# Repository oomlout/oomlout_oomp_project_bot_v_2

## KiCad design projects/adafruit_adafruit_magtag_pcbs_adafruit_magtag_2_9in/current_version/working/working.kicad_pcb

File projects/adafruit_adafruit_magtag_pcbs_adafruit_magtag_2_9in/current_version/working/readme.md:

# adafruit_magtag_pcbs
 
## summary 
* id: adafruit_adafruit_magtag_pcbs_adafruit_magtag_2_9in
* user: adafruit
* name: adafruit_magtag_pcbs
* board: adafruit_magtag_2_9in
* repo: https://github.com/adafruit/Adafruit_MagTag_PCBs

* src_file_repo_sch: 
* src_file_repo_sch_link: https://github.com/adafruit/Adafruit_MagTag_PCBs/tree/main/
* full details link: https://github.com/oomlout/oomlout_oomp_project_bot_v_2/tree/main/projects/adafruit_adafruit_magtag_pcbs_adafruit_magtag_2_9in/current_version/working  

## schematic  
  
[schematic (pdf)](working_schematic.pdf) 

## pcb  

[board (pdf)](working.pdf)  

## working_bom
| Id | Designator | Footprint | Quantity | Designation | Supplier and ref |  | None | 
| --- | --- | --- | --- | --- | --- | --- | --- | 
| 1 | D2,D5,D3 | SOD-123 | 3 | MBR0530 |  |  | [''] | 
| 2 | R7,R20,R5,R2,R9,R1 | 0603-NO | 6 | 10K |  |  | [''] | 
| 3 | C25,C24,C19,C23,C26,C31,C28,C30,C27 | 0805-NO | 9 | 1uF |  |  | [''] | 
| 4 | R18,R16 | 0603-NO | 2 | 1K |  |  | [''] | 
| 5 | C9 | 0805-NO | 1 | 10uF/10V+ |  |  | [''] | 
| 6 | Q3,Q1 | SOT23-R | 2 | DMG3415U-7 |  |  | [''] | 
| 7 | C6,C14,C12 | 0603-NO | 3 | 1uF |  |  | [''] | 
| 8 | R24,R22,R25,R23 | 0603-NO | 4 | DNP |  |  | [''] | 
| 9 | SJ2 | SOLDERJUMPER_2WAY_OPEN_NOPASTE | 1 |  |  |  | [''] | 
| 10 | ON0 | CHIPLED_0603_NOOUTLINE | 1 | GREEN |  |  | [''] | 
| 11 | U4 | SOT23-5 | 1 | AP2112K-3.3 |  |  | [''] | 
| 12 | TP6,TP1,TP7,TP8 | TESTPOINT_ROUND_1.5MM_NO | 4 |  |  |  | [''] | 
| 13 | C8,C7,C11,C13,C17,C10,C18,C3,C4 | 0805-NO | 9 | 10ÂµF |  |  | [''] | 
| 14 | R11,R17,R10 | 0603-NO | 3 | 1Meg |  |  | [''] | 
| 15 | L1 | INDUCTOR_4X4MM_NR401 | 1 | 10uH |  |  | [''] | 
| 16 | D1,D6 | SOD-323 | 2 | 3.6V |  |  | [''] | 
| 17 | U$15 | PCBFEAT-REV-040 | 1 |  |  |  | [''] | 
| 18 | IC2 | SOT23-6 | 1 | PAM8301 |  |  | [''] | 
| 19 | L0 | CHIPLED_0603_NOOUTLINE | 1 | RED |  |  | [''] | 
| 20 | R14,R12 | 0603-NO | 2 | 100k |  |  | [''] | 
| 21 | IC4 | LGA16_3X3MM | 1 | LIS3DH |  |  | [''] | 
| 22 | C1,C20 | 0805-NO | 2 | 10uF |  |  | [''] | 
| 23 | TP2,TP4,TP5,TP3 | SMT_NUT_3MM | 4 | SEWTAP_SMTNUTM3 |  |  | [''] | 
| 24 | R21 | 0805_10MGAP | 1 | DNP |  |  | [''] | 
| 25 | R27,R15,R26 | 0603-NO | 3 | 100K |  |  | [''] | 
| 26 | Q2 | SOT23-R | 1 | DMG3415 |  |  | [''] | 
| 27 | C21,C5,C15,C16,C2 | 0603-NO | 5 | 0.1uF |  |  | [''] | 
| 28 | R19,R6 | 0603-NO | 2 | 47K |  |  | [''] | 
| 29 | U3 | MODULE_ESP32-S2-WROVER | 1 | ESP32-S2-WROVER |  |  | [''] | 
| 30 | CONN1 | JST_SH4 | 1 | STEMMA_I2C_QT |  |  | [''] | 
| 31 | SW3,SW1 | SPST_TACTILE_RA | 2 | RA_TACT |  |  | [''] | 
| 32 | R13 | 0805_10MGAP | 1 | 0.47ohm |  |  | [''] | 
| 33 | U2 | SOT23-5 | 1 | MCP73831T-2ACI/OT |  |  | [''] | 
| 34 | FID3,FID1,FID2,FID4,FID6,FID5 | FIDUCIAL_1MM | 6 | FIDUCIAL_1MM |  |  | [''] | 
| 35 | JP2 | 1X02_ROUND | 1 | UART |  |  | [''] | 
| 36 | C29 | 0805-NO | 1 | 4.7uF/25V |  |  | [''] | 
| 37 | X4 | USB_C_CUSB31-CFM2AX-01-X | 1 | USB C |  |  | [''] | 
| 38 | SW4 | SPDT_SMT_SSSS811101 | 1 | SPDT R/A |  |  | [''] | 
| 39 | SP1 | BUZZER_SMT_7.5MM | 1 | 7.5mm SPK |  |  | [''] | 
| 40 | X1 | JSTPH2_BATT | 1 | JSTPH |  |  | [''] | 
| 41 | D4 | SOD-123 | 1 | MBR540 |  |  | [''] | 
| 42 | SENSE0,SENSE1 | JSTPH3 | 2 | JST PH 3 |  |  | [''] | 
| 43 | R4 | 0603-NO | 1 | 5.1k |  |  | [''] | 
| 44 | U$70 | MAGTAG_FRONT | 1 |  |  |  | [''] | 
| 45 | R8,R3 | 0603-NO | 2 | 5.1K |  |  | [''] | 
| 46 | Q5 | SOT23-3 | 1 | IRLML0100 |  |  | [''] | 
| 47 | CHG1 | CHIPLED_0603_NOOUTLINE | 1 | ORANGE |  |  | [''] | 
| 48 | LED4,LED3,LED2,LED5 | WS2812B_4020 | 4 | WS2812B_4020 |  |  | [''] | 
| 49 | SW2,SW5,SW6,SW7 | TACTILE_3X6MM | 4 |  |  |  | [''] | 
| 50 | U$69 | MAGTAG_BOTTOM | 1 |  |  |  | [''] | 
| 51 | U1 | ALS-PT19-315C | 1 |  |  |  | [''] | 
| 52 | EINK2 | EINK_290IN | 1 | EINK_24PIN_290IN |  |  | [''] | 

## bom_schematic
| Ref | Qnty | Value | Cmp name | Footprint | Description | Vendor | DNP | 
| --- | --- | --- | --- | --- | --- | --- | --- | 
| C1, C20 | 2 | 10uF | CAP_CERAMIC0805-NOOUTLINE | working:0805-NO |  |  |  | 
| C2, C5, C15, C16, C21 | 5 | 0.1uF | CAP_CERAMIC0603_NO | working:0603-NO |  |  |  | 
| C3, C4, C7, C8, C10, C11, C13, C17, C18 | 9 | 10ÂµF | CAP_CERAMIC0805-NOOUTLINE | working:0805-NO |  |  |  | 
| C6, C12, C14 | 3 | 1uF | CAP_CERAMIC0603_NO | working:0603-NO |  |  |  | 
| C9 | 1 | 10uF/10V+ | CAP_CERAMIC0805-NOOUTLINE | working:0805-NO |  |  |  | 
| C19, C23, C24, C25, C26, C27, C28, C30, C31 | 9 | 1uF | CAP_CERAMIC0805-NOOUTLINE | working:0805-NO |  |  |  | 
| C29 | 1 | 4.7uF/25V | CAP_CERAMIC0805-NOOUTLINE | working:0805-NO |  |  |  | 
| CHG1 | 1 | ORANGE | LED0603_NOOUTLINE | working:CHIPLED_0603_NOOUTLINE |  |  |  | 
| CONN1 | 1 | STEMMA_I2C_QT | STEMMA_I2C_QT | working:JST_SH4 |  |  |  | 
| D1, D6 | 2 | 3.6V | DIODE-ZENERSOD323 | working:SOD-323 |  |  |  | 
| D2, D3, D5 | 3 | MBR0530 | DIODE-SCHOTTKYSOD-123 | working:SOD-123 |  |  |  | 
| D4 | 1 | MBR540 | DIODE-SCHOTTKYSOD-123 | working:SOD-123 |  |  |  | 
| EINK2 | 1 | EINK_24PIN_290IN | EINK_24PIN_290IN | working:EINK_290IN |  |  |  | 
| FID1, FID2, FID3, FID4, FID5, FID6 | 6 | FIDUCIAL_1MM | FIDUCIAL_1MM | working:FIDUCIAL_1MM |  |  |  | 
| IC2 | 1 | PAM8301 | PAM8301 | working:SOT23-6 |  |  |  | 
| IC4 | 1 | LIS3DH | ACCEL_LIS3DHTR | working:LGA16_3X3MM |  |  |  | 
| JP2 | 1 | UART | HEADER-1X2ROUND | working:1X02_ROUND |  |  |  | 
| L0 | 1 | RED | LED0603_NOOUTLINE | working:CHIPLED_0603_NOOUTLINE |  |  |  | 
| L1 | 1 | 10uH | INDUCTORNR401 | working:INDUCTOR_4X4MM_NR401 |  |  |  | 
| LED2, LED3, LED4, LED5 | 4 | WS2812B_4020 | WS2812B_4020 | working:WS2812B_4020 |  |  |  | 
| ON0 | 1 | GREEN | LED0603_NOOUTLINE | working:CHIPLED_0603_NOOUTLINE |  |  |  | 
| Q1, Q3 | 2 | DMG3415U-7 | MOSFET-P | working:SOT23-R |  |  |  | 
| Q2 | 1 | DMG3415 | MOSFET-P | working:SOT23-R |  |  |  | 
| Q5 | 1 | IRLML2060TRPBF | IRLML2060TRPBF | working:SOT23-3 |  |  |  | 
| R1, R2, R5, R7, R9, R20 | 6 | 10K | RESISTOR_0603_NOOUT | working:0603-NO |  |  |  | 
| R3, R8 | 2 | 5.1K | RESISTOR_0603_NOOUT | working:0603-NO |  |  |  | 
| R4 | 1 | 5.1k | RESISTOR_0603_NOOUT | working:0603-NO |  |  |  | 
| R6, R19 | 2 | 47K | RESISTOR_0603_NOOUT | working:0603-NO |  |  |  | 
| R10, R11, R17 | 3 | 1Meg | RESISTOR_0603_NOOUT | working:0603-NO |  |  |  | 
| R12, R14 | 2 | 100k | RESISTOR_0603_NOOUT | working:0603-NO |  |  |  | 
| R13 | 1 | 0.47ohm | RESISTOR0805_10MGAP | working:0805_10MGAP |  |  |  | 
| R15, R26, R27 | 3 | 100K | RESISTOR_0603_NOOUT | working:0603-NO |  |  |  | 
| R16, R18 | 2 | 1K | RESISTOR_0603_NOOUT | working:0603-NO |  |  |  | 
| R21 | 1 | DNP | RESISTOR0805_10MGAP | working:0805_10MGAP |  |  |  | 
| R22, R23, R24, R25 | 4 | DNP | RESISTOR_0603_NOOUT | working:0603-NO |  |  |  | 
| SENSE0, SENSE1 | 2 | JST PH 3 | CON_JST_PH_3PIN | working:JSTPH3 |  |  |  | 
| SJ2 | 1 | SOLDERJUMPER_2WAY | SOLDERJUMPER_2WAY | working:SOLDERJUMPER_2WAY_OPEN_NOPASTE |  |  |  | 
| SP1 | 1 | SPEAKER_7.5MM | SPEAKER_7.5MM | working:BUZZER_SMT_7.5MM |  |  |  | 
| SW1, SW3 | 2 | RA_TACT | SWITCH_SPST_TACT_RA | working:SPST_TACTILE_RA |  |  |  | 
| SW2, SW5, SW6, SW7 | 4 | SWITCH_PUSHBUTTON_3.5X6MM | SWITCH_PUSHBUTTON_3.5X6MM | working:TACTILE_3X6MM |  |  |  | 
| SW4 | 1 | SPDT R/A | SWITCH_SPDT | working:SPDT_SMT_SSSS811101 |  |  |  | 
| TP1, TP6, TP7, TP8 | 4 | TESTPOINTROUND1.5MMNO | TESTPOINTROUND1.5MMNO | working:TESTPOINT_ROUND_1.5MM_NO |  |  |  | 
| TP2, TP3, TP4, TP5 | 4 | SEWTAP_SMTNUTM3 | SEWTAP_SMTNUTM3 | working:SMT_NUT_3MM |  |  |  | 
| U1 | 1 | PHOTOTRANSISTOR_PT19-315C | PHOTOTRANSISTOR_PT19-315C | working:ALS-PT19-315C |  |  |  | 
| U2 | 1 | MCP73831T-2ACI/OT | MCP73831/2 | working:SOT23-5 |  |  |  | 
| U3 | 1 | ESP32-S2-WROVER | ESP32-S2-WROVER | working:MODULE_ESP32-S2-WROVER |  |  |  | 
| U4 | 1 | AP2112K-3.3 | VREG_SOT23-5 | working:SOT23-5 |  |  |  | 
| X1 | 1 | JSTPH | CON_JST_PH_2PIN_BATT | working:JSTPH2_BATT |  |  |  | 
| X4 | 1 | USB C | USB_C | working:USB_C_CUSB31-CFM2AX-01-X |  |  |  |

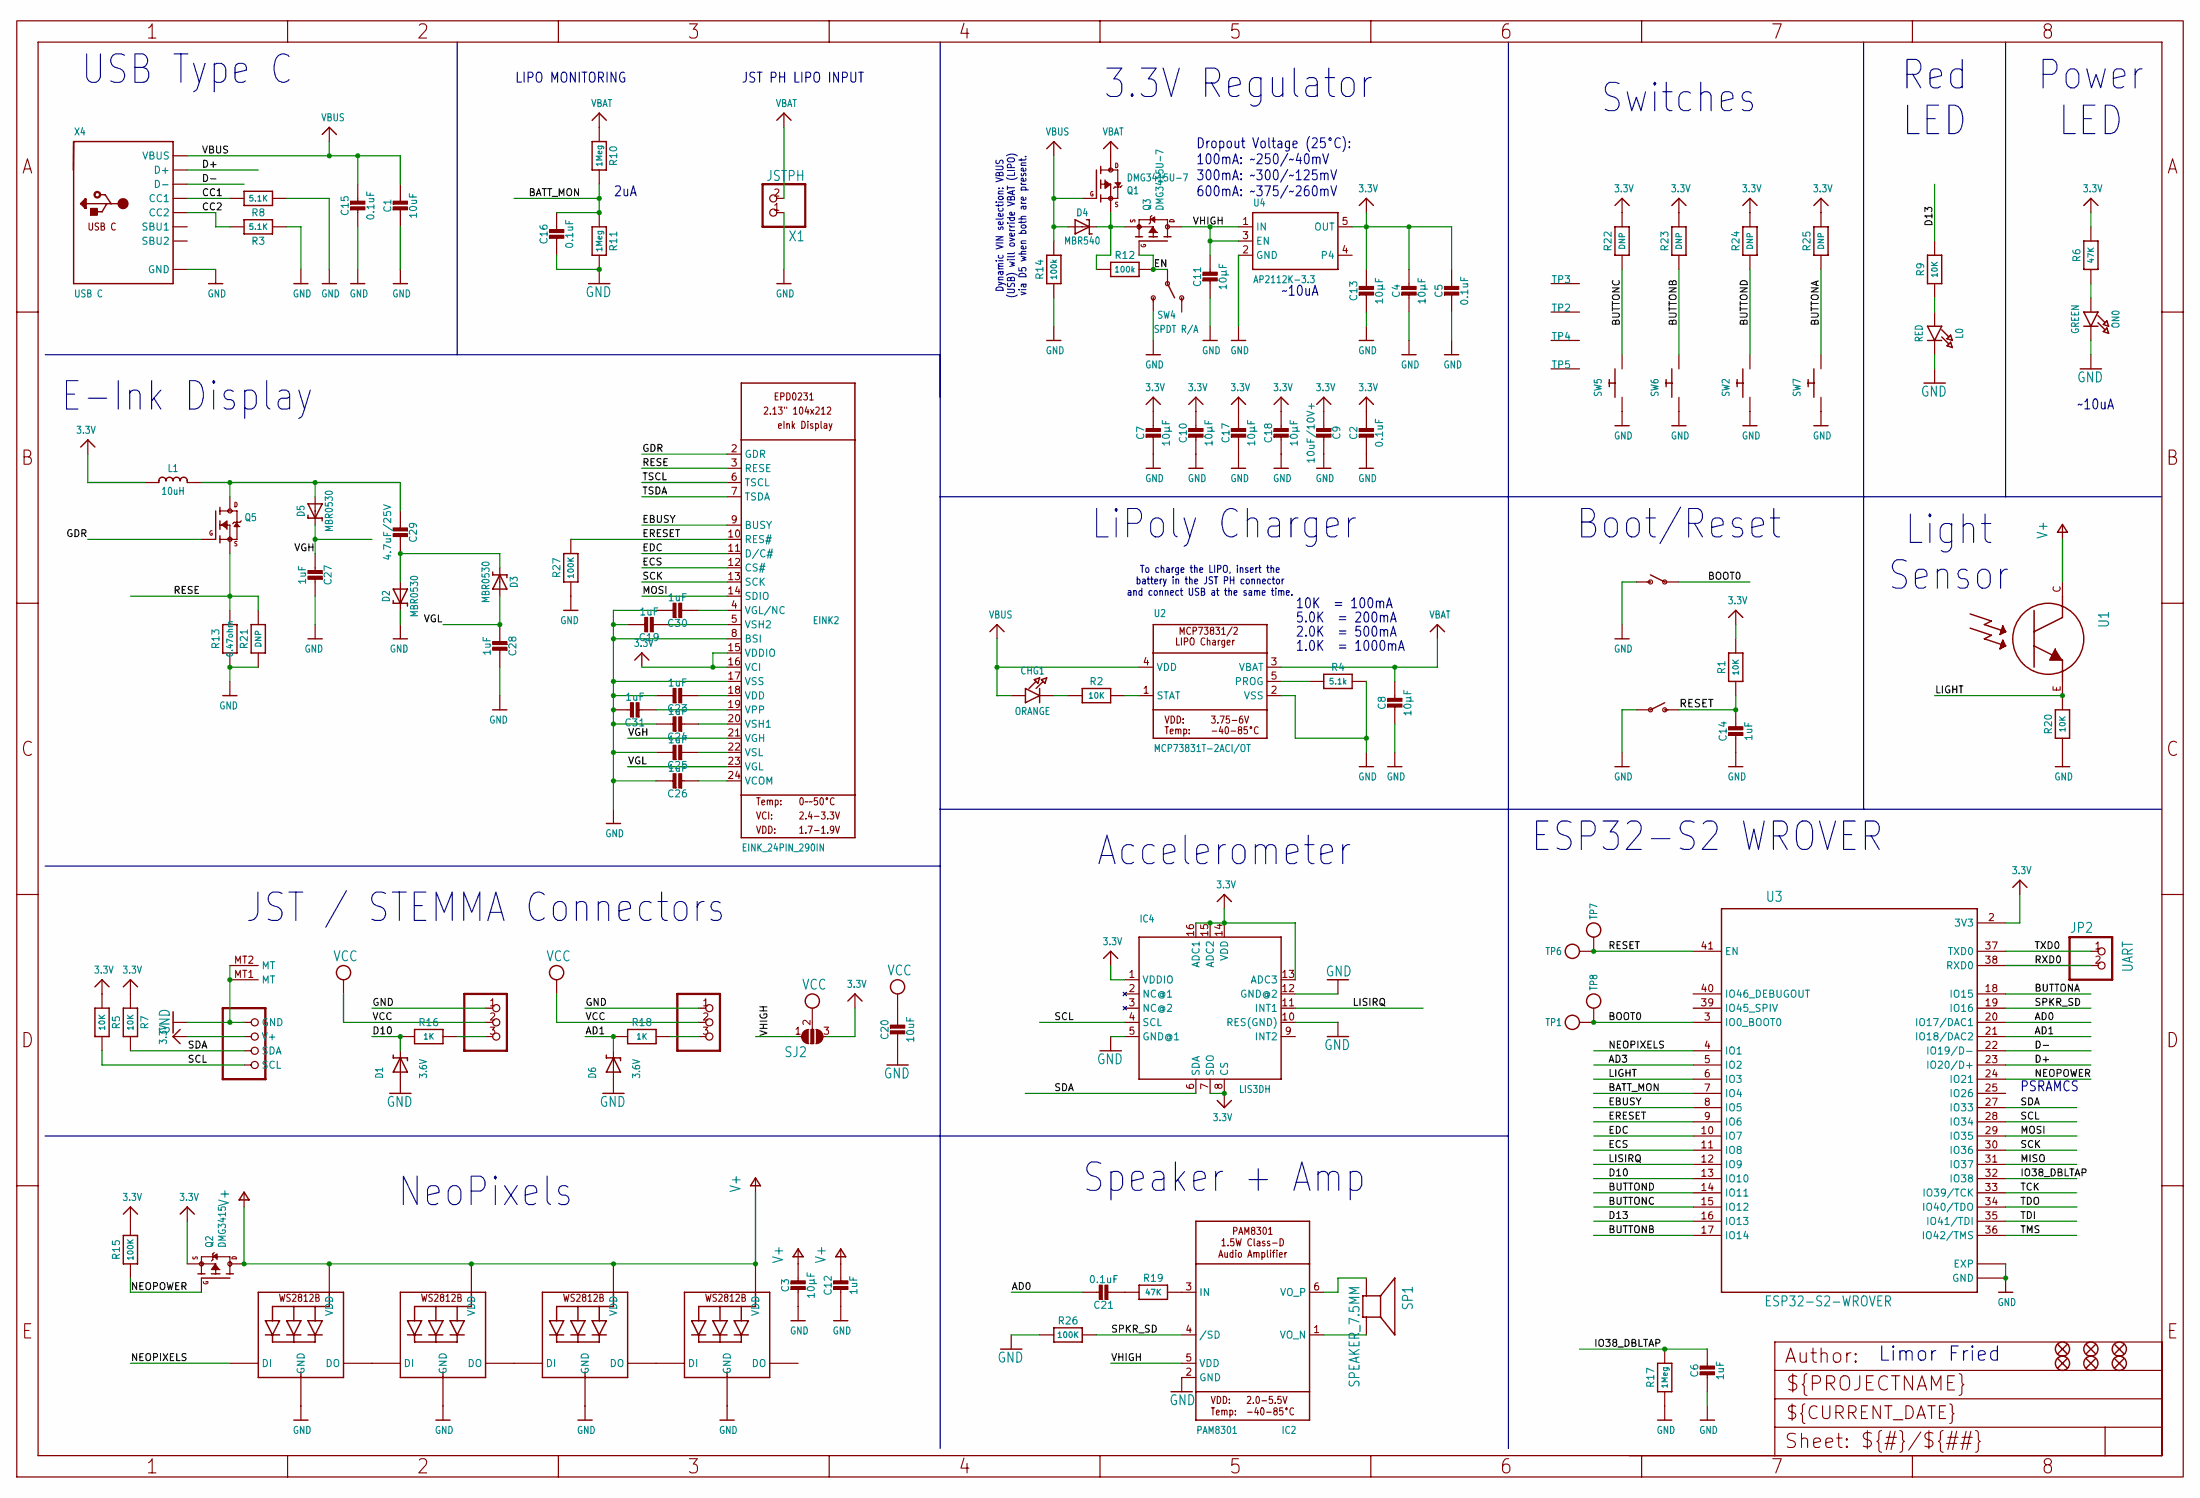
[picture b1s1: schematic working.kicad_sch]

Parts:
C1, C20: 10uF; 0805-NO
C2, C5, C15, C16, C21: 0.1uF; 0603-NO
C3, C4, C7, C8, C10, C11, C13, C17, C18: 10µF; 0805-NO
C6, C12, C14: 1uF; 0603-NO
C9: 10uF/10V+; 0805-NO
C19, C23, C24, C25, C26, C27, C28, C30, C31: 1uF; 0805-NO
C29: 4.7uF/25V; 0805-NO
CHG1: ORANGE; CHIPLED_0603_NOOUTLINE
CONN1: STEMMA_I2C_QT; JST_SH4
D1, D6: 3.6V; SOD-323
D2, D3, D5: MBR0530; SOD-123
D4: MBR540; SOD-123
EINK2: EINK_24PIN_290IN; EINK_290IN
FID1, FID2, FID3, FID4, FID5, FID6: FIDUCIAL_1MM
IC2: PAM8301; SOT23-6
IC4: LIS3DH; LGA16_3X3MM
JP2: UART; 1X02_ROUND
L0: RED; CHIPLED_0603_NOOUTLINE
L1: 10uH; INDUCTOR_4X4MM_NR401
LED2, LED3, LED4, LED5: WS2812B_4020
ON0: GREEN; CHIPLED_0603_NOOUTLINE
Q1, Q3: DMG3415U-7; SOT23-R
Q2: DMG3415; SOT23-R
Q5: IRLML2060TRPBF; SOT23-3
R1, R2, R5, R7, R9, R20: 10K; 0603-NO
R3, R8: 5.1K; 0603-NO
R4: 5.1k; 0603-NO
R6, R19: 47K; 0603-NO
R10, R11, R17: 1Meg; 0603-NO
R12, R14: 100k; 0603-NO
R13: 0.47ohm; 0805_10MGAP
R15, R26, R27: 100K; 0603-NO
R16, R18: 1K; 0603-NO
R21: DNP; 0805_10MGAP
R22, R23, R24, R25: DNP; 0603-NO
SENSE0, SENSE1: JST PH 3; JSTPH3
SJ2: SOLDERJUMPER_2WAY; SOLDERJUMPER_2WAY_OPEN_NOPASTE
SP1: SPEAKER_7.5MM; BUZZER_SMT_7.5MM
SW1, SW3: RA_TACT; SPST_TACTILE_RA
SW2, SW5, SW6, SW7: SWITCH_PUSHBUTTON_3.5X6MM; TACTILE_3X6MM
SW4: SPDT R/A; SPDT_SMT_SSSS811101
TP1, TP6, TP7, TP8: TESTPOINTROUND1.5MMNO; TESTPOINT_ROUND_1.5MM_NO
TP2, TP3, TP4, TP5: SEWTAP_SMTNUTM3; SMT_NUT_3MM
U1: PHOTOTRANSISTOR_PT19-315C; ALS-PT19-315C
U2: MCP73831T-2ACI/OT; SOT23-5
U3: ESP32-S2-WROVER; MODULE_ESP32-S2-WROVER
U4: AP2112K-3.3; SOT23-5
X1: JSTPH; JSTPH2_BATT
X4: USB C; USB_C_CUSB31-CFM2AX-01-X

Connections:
3.3V: C2.1, C4.1, C5.1, C7.1, C9.2, C10.1, C13.1, C17.1, C18.1, CONN1.2 (V+), EINK2.15 (VDDIO), EINK2.16 (VCI), IC4.1 (VDDIO), IC4.7 (SDO), IC4.8 (CS), IC4.13 (ADC3), IC4.14 (VDD), IC4.15 (ADC2), IC4.16 (ADC1), L1.P$2 (2), Q2.2 (S), R1.2, R5.1, R6.2, R7.1, R15.2, R22.2, R23.2, R24.2, R25.2, SJ2.3, U3.2 (3V3), U4.5 (OUT)
A1_JST1: R18.1, SENSE1.3
AD0: C21.1, U3.20 (IO17/DAC1)
AD1: D6.C, R18.2, U3.21 (IO18/DAC2)
AD3: U3.5 (IO2)
BATT_MON: C16.1, R10.2, R11.1, U3.7 (IO4)
BOOT0: SW1.1, TP1.P$1, TP8.P$1, U3.3 (IO0_BOOT0)
BUTTONA: R25.1, SW7.P$2, U3.18 (IO15)
BUTTONB: R23.1, SW6.P$2, U3.17 (IO14)
BUTTONC: R22.1, SW5.P$2, U3.15 (IO12)
BUTTOND: R24.1, SW2.P$2, U3.14 (IO11)
CC1: R8.2, X4.A5 (CC1)
CC2: R3.2, X4.B5 (CC2)
D10: D1.C, R16.2, U3.13 (IO10)
D10_JST: R16.1, SENSE0.3
D13: R9.2, U3.16 (IO13)
D+: U3.23 (IO20/D+), X4.A6 (D+), X4.B6 (D+)
D-: U3.22 (IO19/D-), X4.A7 (D-), X4.B7 (D-)
EBUSY: EINK2.9 (BUSY), U3.8 (IO5)
ECS: EINK2.12 (CS#), U3.11 (IO8)
EDC: EINK2.11 (D/C#), U3.10 (IO7)
EN: Q3.1 (G), R12.2, SW4.B
ERESET: EINK2.10 (RES#), R27.2, U3.9 (IO6)
GDR: EINK2.2 (GDR), Q5.1 (G)
GND: C1.2, C2.2, C3.2, C4.2, C5.2, C6.2, C7.2, C8.2, C9.1, C10.2, C11.2, C12.2, C13.2, C14.2, C15.2, C16.2, C17.2, C18.2, C19.1, C20.2, C23.1, C24.1, C25.1, C26.1, C27.2, C28.2, C30.1, C31.1, CONN1.1 (GND), CONN1.MT1 (MT), CONN1.MT2 (MT), D1.A, D2.C, D6.A, EINK2.8 (BSI), EINK2.17 (VSS), IC2.2 (GND), IC4.5 (GND@1), IC4.10 (RES(GND)), IC4.12 (GND@2), L0.C, LED2.4 (GND), LED3.4 (GND), LED4.4 (GND), LED5.4 (GND), ON0.C, R3.1, R4.2, R8.1, R11.2, R13.2, R14.1, R17.1, R20.1, R21.2, R26.1, R27.1, SENSE0.1, SENSE1.1, SW1.2 (S), SW2.P$1, SW3.1, SW4.C (S), SW5.P$1, SW6.P$1, SW7.P$1, U2.2 (VSS), U3.1 (GND), U3.26 (GND), U3.42 (GND), U3.43_1 (EXP), U3.43_2 (EXP), U3.43_3 (EXP), U3.43_4 (EXP), U3.43_5 (EXP), U3.43_6 (EXP), U3.43_7 (EXP), U3.43_8 (EXP), U3.43_9 (EXP), U3.43_10 (EXP)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
IO38_DBLTAP: C6.1, R17.2, U3.32 (IO38)
LIGHT: R20.2, U1.E, U3.6 (IO3)
LISIRQ: IC4.11 (INT1), U3.12 (IO9)
MISO: U3.31 (IO37)
MOSI: EINK2.14 (SDIO), U3.29 (IO35)
unnamed: L0.A, R9.1
unnamed: LED2.3 (DO), LED3.1 (DI)
unnamed: ON0.A, R6.1
unnamed: CHG1.C, R2.1
unnamed: C21.2, R19.1
unnamed: R2.2, U2.1 (STAT)
unnamed: IC2.3 (IN), R19.2
unnamed: R4.1, U2.5 (PROG)
unnamed: C19.2, EINK2.5 (VSH2)
unnamed: C23.2, EINK2.18 (VDD)
unnamed: C24.2, EINK2.20 (VSH1)
unnamed: LED4.3 (DO), LED5.1 (DI)
unnamed: C29.2, D2.A, D3.C
unnamed: C29.1, D5.A, L1.P$1 (1), Q5.3 (D)
unnamed: C30.2, EINK2.4 (VGL/NC)
unnamed: C31.2, EINK2.19 (VPP)
unnamed: LED3.3 (DO), LED4.1 (DI)
unnamed: IC2.1 (VO_N), SP1.-
unnamed: IC2.6 (VO_P), SP1.+
unnamed: D4.C, Q1.2 (S), Q3.2 (S), R12.1
unnamed: C25.2, EINK2.22 (VSL)
unnamed: C26.2, EINK2.24 (VCOM)
NEOPIXELS: LED2.1 (DI), U3.4 (IO1)
NEOPOWER: Q2.1 (G), R15.1, U3.24 (IO21)
RESE: EINK2.3 (RESE), Q5.2 (S), R13.1, R21.1
RESET: C14.1, R1.1, SW3.2 (S), TP6.P$1, TP7.P$1, U3.41 (EN)
RXD0: JP2.2, U3.38 (RXD0)
SCK: EINK2.13 (SCK), U3.30 (IO36)
SCL: CONN1.4 (SCL), IC4.4 (SCL), R5.2, U3.28 (IO34)
SDA: CONN1.3 (SDA), IC4.6 (SDA), R7.2, U3.27 (IO33)
SPKR_SD: IC2.4 (/SD), R26.2, U3.19 (IO16)
TCK: U3.33 (IO39/TCK)
TDI: U3.35 (IO41/TDI)
TDO: U3.34 (IO40/TDO)
TMS: U3.36 (IO42/TMS)
TSCL: EINK2.6 (TSCL)
TSDA: EINK2.7 (TSDA)
TXD0: JP2.1, U3.37 (TXD0)
V+: C3.1, C12.1, LED2.2 (VDD), LED3.2 (VDD), LED4.2 (VDD), LED5.2 (VDD), Q2.3 (D), U1.C
VBAT: C8.1, Q1.3 (D), R10.1, U2.3 (VBAT), X1.2
VBUS: C1.1, C15.1, CHG1.A, D4.A, Q1.1 (G), R14.2, U2.4 (VDD), X4.A4B9 (VBUS), X4.B4A9 (VBUS)
VCC: C20.1, SENSE0.2, SENSE1.2, SJ2.2
VGH: C27.1, D5.C, EINK2.21 (VGH)
VGL: C28.1, D3.A, EINK2.23 (VGL)
VHIGH: C11.1, IC2.5 (VDD), Q3.3 (D), SJ2.1, U4.1 (IN), U4.3 (EN)

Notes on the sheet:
USB Type C
Dropout Voltage (25°C): 100mA: ~250/~40mV 300mA: ~300/~125mV 600mA: ~375/~260mV
Power LED
Accelerometer
1.0K = 1000mA
JST / STEMMA Connectors
Red LED
Dynamic VIN selection: VBUS (USB) will override VBAT (LIPO) via D5 when both are present.
Limor Fried
Light Sensor
~10uA
LiPoly Charger
Boot/Reset
2uA
5.0K = 200mA
ESP32-S2 WROVER
Switches
3.3V Regulator
Speaker + Amp
LIPO MONITORING
E-Ink Display
To charge the LIPO, insert the battery in the JST PH connector and connect USB at the same time.
NeoPixels
JST PH LIPO INPUT
10K = 100mA
2.0K = 500mA
PSRAMCS

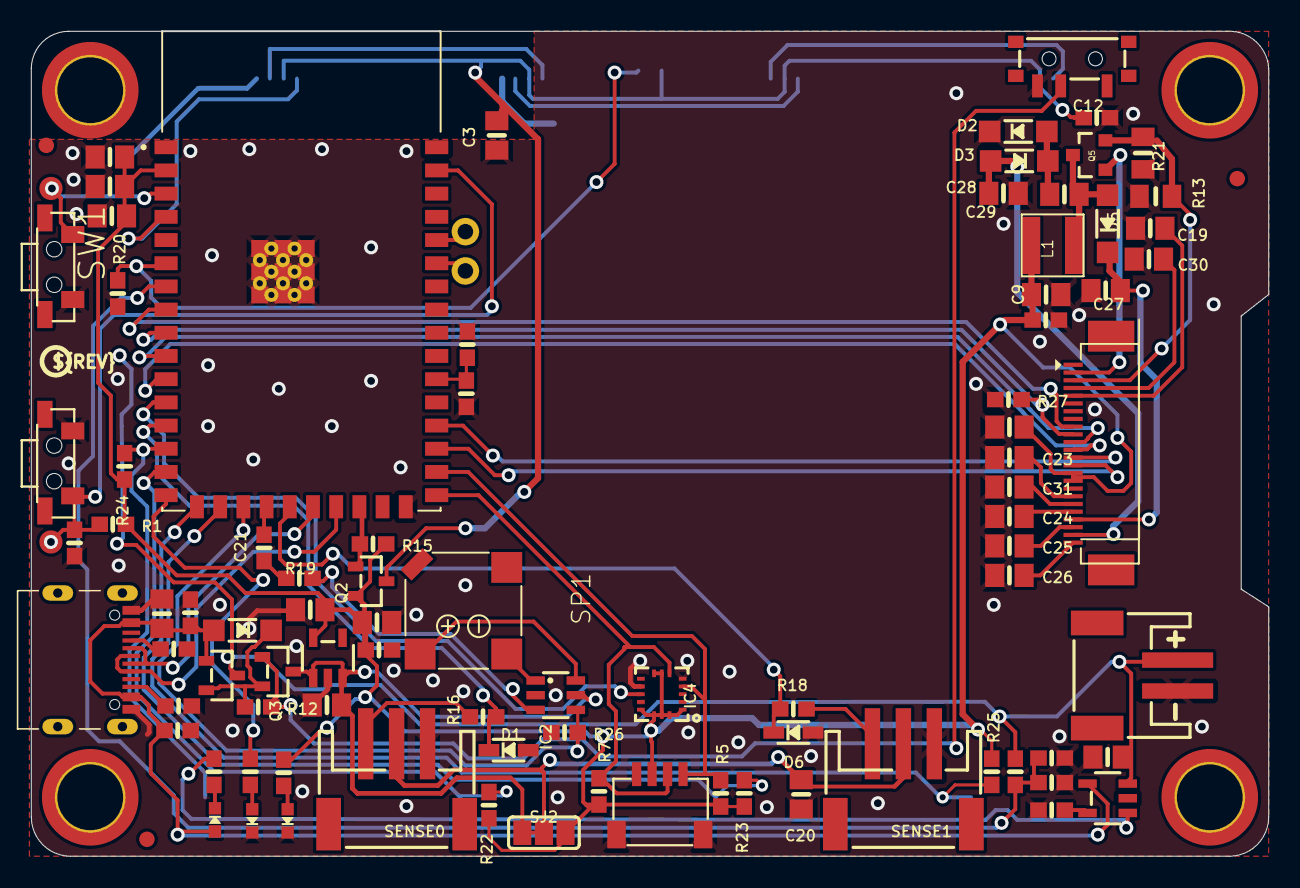
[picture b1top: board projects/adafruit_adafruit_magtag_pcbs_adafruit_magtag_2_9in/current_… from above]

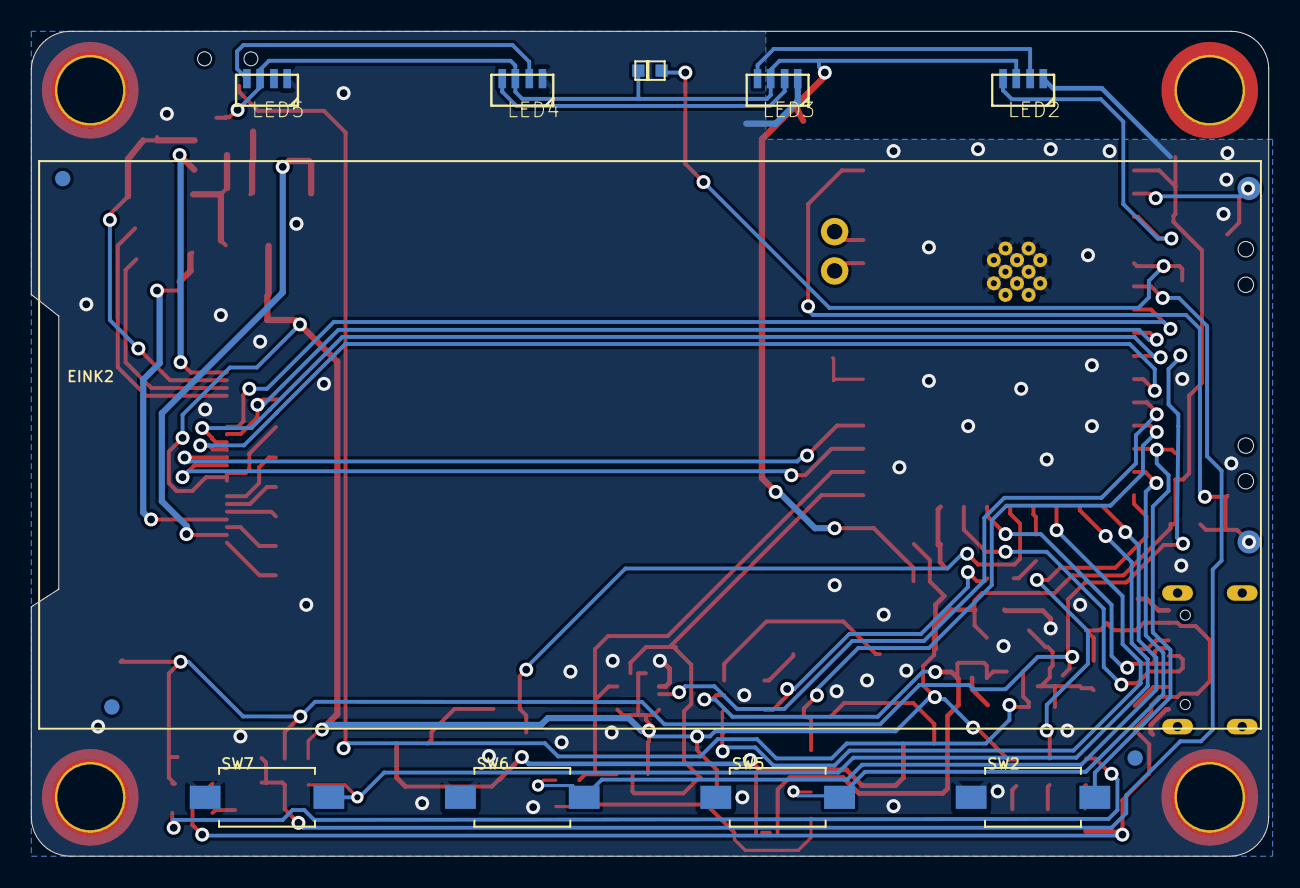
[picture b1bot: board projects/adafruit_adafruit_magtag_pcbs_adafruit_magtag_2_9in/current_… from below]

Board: 2 copper layers, 80.0 x 53.3 mm, 114 parts (16 on the bottom side), 67 nets.

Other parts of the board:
U$15: PCBFEAT-REV-040
U$69: MAGTAG_BOTTOM
U$70: MAGTAG_FRONT

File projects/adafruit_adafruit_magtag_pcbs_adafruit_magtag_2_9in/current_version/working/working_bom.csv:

"Id";"Designator";"Footprint";"Quantity";"Designation";"Supplier and ref";
1;"D2,D5,D3";"SOD-123";3;"MBR0530";;;
2;"R7,R20,R5,R2,R9,R1";"0603-NO";6;"10K";;;
3;"C25,C24,C19,C23,C26,C31,C28,C30,C27";"0805-NO";9;"1uF";;;
4;"R18,R16";"0603-NO";2;"1K";;;
5;"C9";"0805-NO";1;"10uF/10V+";;;
6;"Q3,Q1";"SOT23-R";2;"DMG3415U-7";;;
7;"C6,C14,C12";"0603-NO";3;"1uF";;;
8;"R24,R22,R25,R23";"0603-NO";4;"DNP";;;
9;"SJ2";"SOLDERJUMPER_2WAY_OPEN_NOPASTE";1;"";;;
10;"ON0";"CHIPLED_0603_NOOUTLINE";1;"GREEN";;;
11;"U4";"SOT23-5";1;"AP2112K-3.3";;;
12;"TP6,TP1,TP7,TP8";"TESTPOINT_ROUND_1.5MM_NO";4;"";;;
13;"C8,C7,C11,C13,C17,C10,C18,C3,C4";"0805-NO";9;"10µF";;;
14;"R11,R17,R10";"0603-NO";3;"1Meg";;;
15;"L1";"INDUCTOR_4X4MM_NR401";1;"10uH";;;
16;"D1,D6";"SOD-323";2;"3.6V";;;
17;"U$15";"PCBFEAT-REV-040";1;"";;;
18;"IC2";"SOT23-6";1;"PAM8301";;;
19;"L0";"CHIPLED_0603_NOOUTLINE";1;"RED";;;
20;"R14,R12";"0603-NO";2;"100k";;;
21;"IC4";"LGA16_3X3MM";1;"LIS3DH";;;
22;"C1,C20";"0805-NO";2;"10uF";;;
23;"TP2,TP4,TP5,TP3";"SMT_NUT_3MM";4;"SEWTAP_SMTNUTM3";;;
24;"R21";"0805_10MGAP";1;"DNP";;;
25;"R27,R15,R26";"0603-NO";3;"100K";;;
26;"Q2";"SOT23-R";1;"DMG3415";;;
27;"C21,C5,C15,C16,C2";"0603-NO";5;"0.1uF";;;
28;"R19,R6";"0603-NO";2;"47K";;;
29;"U3";"MODULE_ESP32-S2-WROVER";1;"ESP32-S2-WROVER";;;
30;"CONN1";"JST_SH4";1;"STEMMA_I2C_QT";;;
31;"SW3,SW1";"SPST_TACTILE_RA";2;"RA_TACT";;;
32;"R13";"0805_10MGAP";1;"0.47ohm";;;
33;"U2";"SOT23-5";1;"MCP73831T-2ACI/OT";;;
34;"FID3,FID1,FID2,FID4,FID6,FID5";"FIDUCIAL_1MM";6;"FIDUCIAL_1MM";;;
35;"JP2";"1X02_ROUND";1;"UART";;;
36;"C29";"0805-NO";1;"4.7uF/25V";;;
37;"X4";"USB_C_CUSB31-CFM2AX-01-X";1;"USB C";;;
38;"SW4";"SPDT_SMT_SSSS811101";1;"SPDT R/A";;;
39;"SP1";"BUZZER_SMT_7.5MM";1;"7.5mm SPK";;;
40;"X1";"JSTPH2_BATT";1;"JSTPH";;;
41;"D4";"SOD-123";1;"MBR540";;;
42;"SENSE0,SENSE1";"JSTPH3";2;"JST PH 3";;;
43;"R4";"0603-NO";1;"5.1k";;;
44;"U$70";"MAGTAG_FRONT";1;"";;;
45;"R8,R3";"0603-NO";2;"5.1K";;;
46;"Q5";"SOT23-3";1;"IRLML0100";;;
47;"CHG1";"CHIPLED_0603_NOOUTLINE";1;"ORANGE";;;
48;"LED4,LED3,LED2,LED5";"WS2812B_4020";4;"WS2812B_4020";;;
49;"SW2,SW5,SW6,SW7";"TACTILE_3X6MM";4;"";;;
50;"U$69";"MAGTAG_BOTTOM";1;"";;;
51;"U1";"ALS-PT19-315C";1;"";;;
52;"EINK2";"EINK_290IN";1;"EINK_24PIN_290IN";;;

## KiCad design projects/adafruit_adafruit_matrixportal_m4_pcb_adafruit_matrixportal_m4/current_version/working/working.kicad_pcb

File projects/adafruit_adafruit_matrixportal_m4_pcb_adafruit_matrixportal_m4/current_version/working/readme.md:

# adafruit_matrixportal_m4_pcb
 
## summary 
* id: adafruit_adafruit_matrixportal_m4_pcb_adafruit_matrixportal_m4
* user: adafruit
* name: adafruit_matrixportal_m4_pcb
* board: adafruit_matrixportal_m4
* repo: https://github.com/adafruit/Adafruit-MatrixPortal-M4-PCB

* src_file_repo_sch: 
* src_file_repo_sch_link: https://github.com/adafruit/Adafruit-MatrixPortal-M4-PCB/tree/main/
* full details link: https://github.com/oomlout/oomlout_oomp_project_bot_v_2/tree/main/projects/adafruit_adafruit_matrixportal_m4_pcb_adafruit_matrixportal_m4/current_version/working  

## schematic  
  
[schematic (pdf)](working_schematic.pdf) 

## pcb  

[board (pdf)](working.pdf)  

## working_bom
| Id | Designator | Footprint | Quantity | Designation | Supplier and ref |  | None | 
| --- | --- | --- | --- | --- | --- | --- | --- | 
| 1 | R4,R9 | 0603-NO | 2 | 1K |  |  | [''] | 
| 2 | SENSE0 | JSTPH3 | 1 | JST PH 3 |  |  | [''] | 
| 3 | C3,C7,C2,C4,C19,C1,C18,C20 | 0805-NO | 8 | 10uF |  |  | [''] | 
| 4 | L0 | CHIPLED_0603_NOOUTLINE | 1 | RED |  |  | [''] | 
| 5 | U2 | SOT23-DBV | 1 | AP2112K-3.3 |  |  | [''] | 
| 6 | D2 | SOD-323 | 1 | 3.6V |  |  | [''] | 
| 7 | C16,C6,C15,C11,C8,C10,C14 | 0603-NO | 7 | .1u |  |  | [''] | 
| 8 | C5,C17,C13 | 0603-NO | 3 | 0.1uF |  |  | [''] | 
| 9 | U$44 | PCBFEAT-REV-040 | 1 |  |  |  | [''] | 
| 10 | RST0,UP0,DOWN0 | SPST_TACTILE_RA | 3 | TL3330AF260QG |  |  | [''] | 
| 11 | TP2,TP1 | SMT_NUT_3MM | 2 | SEWTAP_SMTNUTM3 |  |  | [''] | 
| 12 | LED1 | LED3535 | 1 | WS2812B3535 |  |  | [''] | 
| 13 | R15,R5,R1,R2,R6,R7 | 0603-NO | 6 | 10K |  |  | [''] | 
| 14 | U3 | SOIC8_208MIL | 1 | GD25Q16 |  |  | [''] | 
| 15 | CONN1 | JST_SH4 | 1 | STEMMA_I2C_QT |  |  | [''] | 
| 16 | X6 | WROOM32 | 1 | ESP32_WROOM32 |  |  | [''] | 
| 17 | R8,R3 | 0603-NO | 2 | 5.1K |  |  | [''] | 
| 18 | UNK3VON0,UNK5VON0 | CHIPLED_0805_NOOUTLINE | 2 | GREEN |  |  | [''] | 
| 19 | SJ2,SJ1 | SOLDERJUMPER_2WAY_OPEN_NOPASTE | 2 |  |  |  | [''] | 
| 20 | FID2,FID1,FID3,FID4 | FIDUCIAL_1MM | 4 | FIDUCIAL_1MM |  |  | [''] | 
| 21 | JP1 | 1X11_ROUND | 1 |  |  |  | [''] | 
| 22 | U$45 | MATRIXPORTAL_TOP | 1 |  |  |  | [''] | 
| 23 | U$1 | PQFN64-1 | 1 | ATSAMD51J19 |  |  | [''] | 
| 24 | R10 | RESPACK_4X0603 | 1 | 5.1K |  |  | [''] | 
| 25 | PC2 | PANASONIC_D | 1 | 47uF+/6.3V+ |  |  | [''] | 
| 26 | C9 | 0603-NO | 1 | 1uF |  |  | [''] | 
| 27 | U5,U1 | TSSOP20 | 2 | 74AHCT245 |  |  | [''] | 
| 28 | X5 | USB_C_CUSB31-CFM2AX-01-X | 1 | USB TYPE C |  |  | [''] | 
| 29 | U4 | LGA16_3X3MM | 1 | LIS3DHTR |  |  | [''] | 
| 30 | X1 | 2X08_SMTTHM_RGBMATRIX | 1 | RGBMATRIX_THMSMT |  |  | [''] | 
| 31 | U$41 | MATRIXPORTAL_BOT | 1 |  |  |  | [''] | 

## bom_schematic
| Ref | Qnty | Value | Cmp name | Footprint | Description | Vendor | DNP | 
| --- | --- | --- | --- | --- | --- | --- | --- | 
| C1, C2, C3, C4, C7, C18, C19, C20 | 8 | 10uF | CAP_CERAMIC0805-NOOUTLINE | working:0805-NO |  |  |  | 
| C5, C13, C17 | 3 | 0.1uF | CAP_CERAMIC0603_NO | working:0603-NO |  |  |  | 
| C6, C8, C10, C11, C14, C15, C16 | 7 | .1u | CAP_CERAMIC0603_NO | working:0603-NO |  |  |  | 
| C9 | 1 | 1uF | CAP_CERAMIC0603_NO | working:0603-NO |  |  |  | 
| CONN1 | 1 | STEMMA_I2C_QT | STEMMA_I2C_QT | working:JST_SH4 |  |  |  | 
| D2 | 1 | 3.6V | DIODE-ZENERSOD323 | working:SOD-323 |  |  |  | 
| DOWN0 | 1 | TL3330AF260QG | SWITCH_SPST_TACT_RA | working:SPST_TACTILE_RA |  |  |  | 
| FID1, FID2, FID3, FID4 | 4 | FIDUCIAL_1MM | FIDUCIAL_1MM | working:FIDUCIAL_1MM |  |  |  | 
| JP1 | 1 | HEADER-1X11 | HEADER-1X11 | working:1X11_ROUND |  |  |  | 
| L0 | 1 | RED | LED0603_NOOUTLINE | working:CHIPLED_0603_NOOUTLINE |  |  |  | 
| LED1 | 1 | WS2812B3535 | WS2812B3535 | working:LED3535 |  |  |  | 
| PC2 | 1 | 47uF+/6.3V+ | CAP_ELECTROLYTICPANASONIC_D | working:PANASONIC_D |  |  |  | 
| R1, R2, R5, R6, R7, R15 | 6 | 10K | RESISTOR_0603_NOOUT | working:0603-NO |  |  |  | 
| R3, R8 | 2 | 5.1K | RESISTOR_0603_NOOUT | working:0603-NO |  |  |  | 
| R4, R9 | 2 | 1K | RESISTOR_0603_NOOUT | working:0603-NO |  |  |  | 
| R10 | 1 | 5.1K | RESISTOR_4PACK | working:RESPACK_4X0603 |  |  |  | 
| RST0 | 1 | TL3330AF260QG | SWITCH_SPST_TACT_RA | working:SPST_TACTILE_RA |  |  |  | 
| SENSE0 | 1 | JST PH 3 | CON_JST_PH_3PIN | working:JSTPH3 |  |  |  | 
| SJ1, SJ2 | 2 | SOLDERJUMPER_2WAY | SOLDERJUMPER_2WAY | working:SOLDERJUMPER_2WAY_OPEN_NOPASTE |  |  |  | 
| TP1, TP2 | 2 | SEWTAP_SMTNUTM3 | SEWTAP_SMTNUTM3 | working:SMT_NUT_3MM |  |  |  | 
| U1, U5 | 2 | 74AHCT245 | 74LCX245 | working:TSSOP20 |  |  |  | 
| U2 | 1 | LP2985-XXDBVR | LP2985-XXDBVR | working:SOT23-DBV |  |  |  | 
| U3 | 1 | GD25Q16 | SPIFLASH_8PIN208MIL | working:SOIC8_208MIL |  |  |  | 
| U4 | 1 | LIS3DHTR | ACCEL_LIS3DHTR | working:LGA16_3X3MM |  |  |  | 
| U$1 | 1 | ATSAMD51J | ATSAMD51J | working:PQFN64-1 |  |  |  | 
| UNK3VON0 | 1 | GREEN | LED0805_NOOUTLINE | working:CHIPLED_0805_NOOUTLINE |  |  |  | 
| UNK5VON0 | 1 | GREEN | LED0805_NOOUTLINE | working:CHIPLED_0805_NOOUTLINE |  |  |  | 
| UP0 | 1 | TL3330AF260QG | SWITCH_SPST_TACT_RA | working:SPST_TACTILE_RA |  |  |  | 
| X1 | 1 | RGBMATRIX_THMSMT | RGBMATRIX_THMSMT | working:2X08_SMTTHM_RGBMATRIX |  |  |  | 
| X5 | 1 | USB TYPE C | USB_C | working:USB_C_CUSB31-CFM2AX-01-X |  |  |  | 
| X6 | 1 | ESP32_WROOM32 | ESP32_WROOM32 | working:WROOM32 |  |  |  |

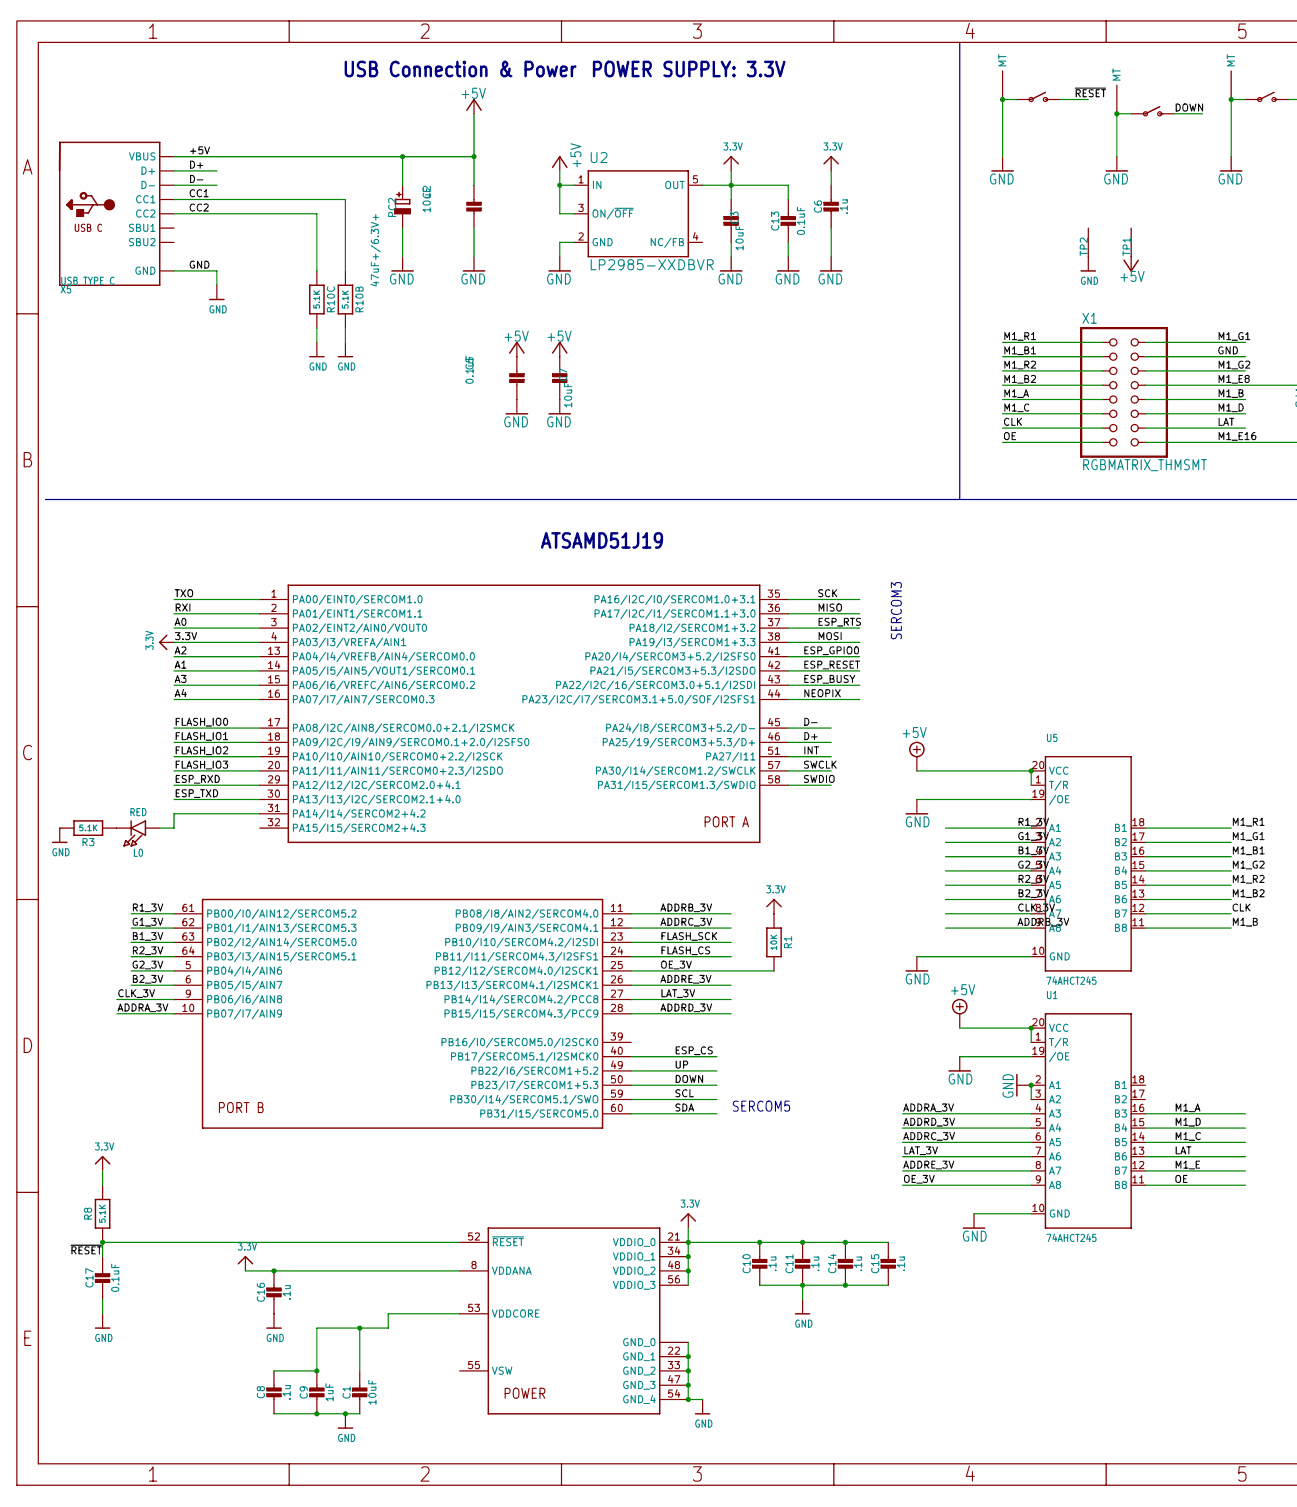
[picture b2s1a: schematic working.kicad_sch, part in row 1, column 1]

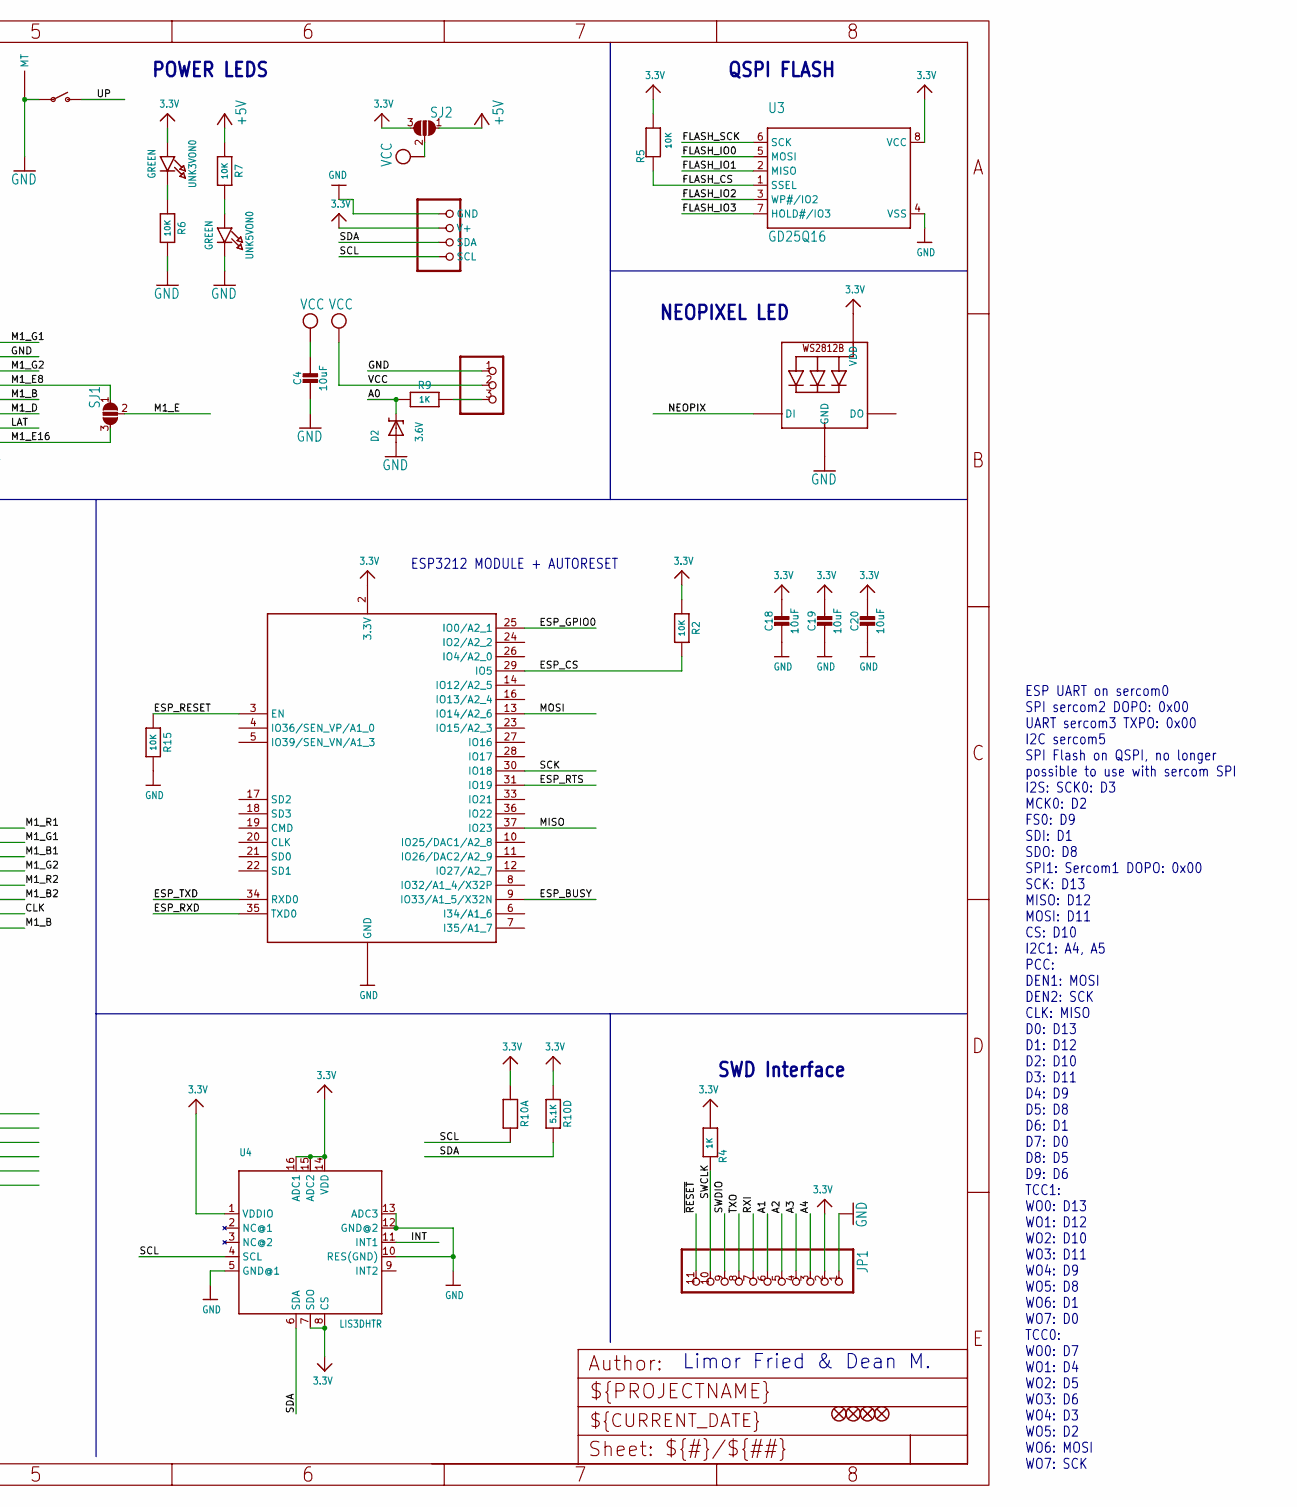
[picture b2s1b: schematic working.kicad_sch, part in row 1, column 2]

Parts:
C1, C2, C3, C4, C7, C18, C19, C20: 10uF; 0805-NO
C5, C13, C17: 0.1uF; 0603-NO
C6, C8, C10, C11, C14, C15, C16: .1u; 0603-NO
C9: 1uF; 0603-NO
CONN1: STEMMA_I2C_QT; JST_SH4
D2: 3.6V; SOD-323
DOWN0: TL3330AF260QG; SPST_TACTILE_RA
FID1, FID2, FID3, FID4: FIDUCIAL_1MM
JP1: HEADER-1X11; 1X11_ROUND
L0: RED; CHIPLED_0603_NOOUTLINE
LED1: WS2812B3535; LED3535
PC2: 47uF+/6.3V+; PANASONIC_D
R1, R2, R5, R6, R7, R15: 10K; 0603-NO
R3, R8: 5.1K; 0603-NO
R4, R9: 1K; 0603-NO
R10: 5.1K; RESPACK_4X0603
RST0: TL3330AF260QG; SPST_TACTILE_RA
SENSE0: JST PH 3; JSTPH3
SJ1, SJ2: SOLDERJUMPER_2WAY; SOLDERJUMPER_2WAY_OPEN_NOPASTE
TP1, TP2: SEWTAP_SMTNUTM3; SMT_NUT_3MM
U1, U5: 74AHCT245; TSSOP20
U2: LP2985-XXDBVR; SOT23-DBV
U3: GD25Q16; SOIC8_208MIL
U4: LIS3DHTR; LGA16_3X3MM
U$1: ATSAMD51J; PQFN64-1
UNK3VON0, UNK5VON0: GREEN; CHIPLED_0805_NOOUTLINE
UP0: TL3330AF260QG; SPST_TACTILE_RA
X1: RGBMATRIX_THMSMT; 2X08_SMTTHM_RGBMATRIX
X5: USB TYPE C; USB_C_CUSB31-CFM2AX-01-X
X6: ESP32_WROOM32; WROOM32

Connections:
3.3V: C3.2, C6.2, C10.2, C11.2, C13.1, C14.2, C15.2, C16.2, C18.1, C19.1, C20.1, CONN1.2 (V+), JP1.2, LED1.2 (VDD), R1.1, R2.1, R4.2, R5.2, R8.2, R10.1, R10.4 (1), SJ2.3, U2.5 (OUT), U3.8 (VCC), U4.1 (VDDIO), U4.7 (SDO), U4.8 (CS), U4.14 (VDD), U4.15 (ADC2), U4.16 (ADC1), U$1.4 (PA03/I3/VREFA/AIN1), U$1.8 (VDDANA), U$1.21 (VDDIO_0), U$1.34 (VDDIO_1), U$1.48 (VDDIO_2), U$1.56 (VDDIO_3), UNK3VON0.A, X6.2 (3.3V)
+5V: C2.2, C5.2, C7.2, PC2.+, R7.1, SJ2.1, TP1.P$1, U1.1 (T/R), U1.20 (VCC), U2.1 (IN), U2.3 (ON/~OFF), U5.1 (T/R), U5.20 (VCC), X5.A4B9 (VBUS), X5.B4A9 (VBUS)
A0: D2.C, R9.2, U$1.3 (PA02/EINT2/AIN0/VOUT0)
A0_JST: R9.1, SENSE0.3
A1: JP1.6, U$1.14 (PA05/I5/AIN5/VOUT1/SERCOM0.1)
A2: JP1.5, U$1.13 (PA04/I4/VREFB/AIN4/SERCOM0.0)
A3: JP1.4, U$1.15 (PA06/I6/VREFC/AIN6/SERCOM0.2)
A4: JP1.3, U$1.16 (PA07/I7/AIN7/SERCOM0.3)
ADDRA_3V: U1.4 (A3), U$1.10 (PB07/I7/AIN9)
ADDRB_3V: U5.9 (A8), U$1.11 (PB08/I8/AIN2/SERCOM4.0)
ADDRC_3V: U1.6 (A5), U$1.12 (PB09/I9/AIN3/SERCOM4.1)
ADDRD_3V: U1.5 (A4), U$1.28 (PB15/I15/SERCOM4.3/PCC9)
ADDRE_3V: U1.8 (A7), U$1.26 (PB13/I13/SERCOM4.1/I2SMCK1)
B1_3V: U5.4 (A3), U$1.63 (PB02/I2/AIN14/SERCOM5.0)
B2_3V: U5.7 (A6), U$1.6 (PB05/I5/AIN7)
CC1: R10.2 (1), X5.A5 (CC1)
CC2: R10.3 (1), X5.B5 (CC2)
CLK: U5.12 (B7), X1.13, X1.13S (13)
CLK_3V: U5.8 (A7), U$1.9 (PB06/I6/AIN8)
D+: U$1.46 (PA25/19/SERCOM3+5.3/D+), X5.A6 (D+), X5.B6 (D+)
D-: U$1.45 (PA24/I8/SERCOM3+5.2/D-), X5.A7 (D-), X5.B7 (D-)
DOWN: DOWN0.2 (S), U$1.50 (PB23/I7/SERCOM1+5.3)
ESP_BUSY: U$1.43 (PA22/I2C/16/SERCOM3.0+5.1/I2SDI), X6.9 (IO33/A1_5/X32N)
ESP_CS: R2.2, U$1.40 (PB17/SERCOM5.1/I2SMCK0), X6.29 (IO5)
ESP_GPIO0: U$1.41 (PA20/I4/SERCOM3+5.2/I2SFS0), X6.25 (IO0/A2_1)
ESP_RESET: R15.1, U$1.42 (PA21/I5/SERCOM3+5.3/I2SDO), X6.3 (EN)
ESP_RTS: U$1.37 (PA18/I2/SERCOM1+3.2), X6.31 (IO19)
ESP_RXD: U$1.29 (PA12/I12/I2C/SERCOM2.0+4.1), X6.35 (TXD0)
ESP_TXD: U$1.30 (PA13/I13/I2C/SERCOM2.1+4.0), X6.34 (RXD0)
FLASH_CS: R5.1, U3.1 (SSEL), U$1.24 (PB11/I11/SERCOM4.3/I2SFS1)
FLASH_IO0: U3.5 (MOSI), U$1.17 (PA08/I2C/AIN8/SERCOM0.0+2.1/I2SMCK)
FLASH_IO1: U3.2 (MISO), U$1.18 (PA09/I2C/I9/AIN9/SERCOM0.1+2.0/I2SFS0)
FLASH_IO2: U3.3 (WP#/IO2), U$1.19 (PA10/I10/AIN10/SERCOM0+2.2/I2SCK)
FLASH_IO3: U3.7 (HOLD#/IO3), U$1.20 (PA11/I11/AIN11/SERCOM0+2.3/I2SDO)
FLASH_SCK: U3.6 (SCK), U$1.23 (PB10/I10/SERCOM4.2/I2SDI)
G1_3V: U5.3 (A2), U$1.62 (PB01/I1/AIN13/SERCOM5.3)
G2_3V: U5.5 (A4), U$1.5 (PB04/I4/AIN6)
GND: C1.2, C2.1, C3.1, C4.2, C5.1, C6.1, C7.1, C8.1, C9.2, C10.1, C11.1, C13.2, C14.1, C15.1, C16.1, C17.1, C18.2, C19.2, C20.2, CONN1.1 (GND), D2.A, DOWN0.1, DOWN0.MT1 (MT), DOWN0.MT2 (MT), JP1.1, LED1.4 (GND), PC2.-, R3.2, R6.2, R10.6 (2), R10.7 (2), R15.2, RST0.1, RST0.MT1 (MT), RST0.MT2 (MT), SENSE0.1, TP2.P$1, U1.2 (A1), U1.3 (A2), U1.10 (GND), U1.19 (/OE), U2.2 (GND), U3.4 (VSS), U4.5 (GND@1), U4.10 (RES(GND)), U4.12 (GND@2), U4.13 (ADC3), U5.10 (GND), U5.19 (/OE), U$1.7 (GND_0), U$1.22 (GND_1), U$1.33 (GND_2), U$1.47 (GND_3), U$1.54 (GND_4), U$1.EXP (GND_0), UNK5VON0.C, UP0.1, UP0.MT1 (MT), UP0.MT2 (MT), X1.4, X1.4S (4), X5.A1B12 (GND), X5.B1A12 (GND), X6.1 (GND), X6.15 (GND), X6.38 (GND), X6.P$1 (GND)
INT: U4.11 (INT1), U$1.51 (PA27/I11)
LAT: U1.13 (B6), X1.14, X1.14S (14)
LAT_3V: U1.7 (A6), U$1.27 (PB14/I14/SERCOM4.2/PCC8)
M1_A: U1.16 (B3), X1.9, X1.9S (9)
M1_B: U5.11 (B8), X1.10, X1.10S (10)
M1_B1: U5.16 (B3), X1.3, X1.3S (3)
M1_B2: U5.13 (B6), X1.7, X1.7S (7)
M1_C: U1.14 (B5), X1.11, X1.11S (11)
M1_D: U1.15 (B4), X1.12, X1.12S (12)
M1_E: SJ1.2, U1.12 (B7)
M1_E8: SJ1.1, X1.8, X1.8S (8)
M1_E16: SJ1.3, X1.16, X1.16S (16)
M1_G1: U5.17 (B2), X1.2, X1.2S (2)
M1_G2: U5.15 (B4), X1.6, X1.6S (6)
M1_R1: U5.18 (B1), X1.1, X1.1S (1)
M1_R2: U5.14 (B5), X1.5, X1.5S (5)
MISO: U$1.36 (PA17/I2C/I1/SERCOM1.1+3.0), X6.37 (IO23)
MOSI: U$1.38 (PA19/I3/SERCOM1+3.3), X6.13 (IO14/A2_6)
unnamed: R7.2, UNK5VON0.A
unnamed: R6.1, UNK3VON0.C
unnamed: L0.A, U$1.31 (PA14/I14/SERCOM2+4.2)
unnamed: L0.C, R3.1
NEOPIX: LED1.1 (DI), U$1.44 (PA23/I2C/I7/SERCOM3.1+5.0/SOF/I2SFS1)
OE: U1.11 (B8), X1.15, X1.15S (15)
OE_3V: R1.2, U1.9 (A8), U$1.25 (PB12/I12/SERCOM4.0/I2SCK1)
R1_3V: U5.2 (A1), U$1.61 (PB00/I0/AIN12/SERCOM5.2)
R2_3V: U5.6 (A5), U$1.64 (PB03/I3/AIN15/SERCOM5.1)
RXI: JP1.7, U$1.2 (PA01/EINT1/SERCOM1.1)
SCK: U$1.35 (PA16/I2C/I0/SERCOM1.0+3.1), X6.30 (IO18)
SCL: CONN1.4 (SCL), R10.8 (2), U4.4 (SCL), U$1.59 (PB30/I14/SERCOM5.1/SWO)
SDA: CONN1.3 (SDA), R10.5 (2), U4.6 (SDA), U$1.60 (PB31/I15/SERCOM5.0)
SWCLK: JP1.10, R4.1, U$1.57 (PA30/I14/SERCOM1.2/SWCLK)
SWDIO: JP1.9, U$1.58 (PA31/I15/SERCOM1.3/SWDIO)
TXO: JP1.8, U$1.1 (PA00/EINT0/SERCOM1.0)
UP: U$1.49 (PB22/I6/SERCOM1+5.2), UP0.2 (S)
VCC: C4.1, SENSE0.2, SJ2.2
VDDCORE: C1.1, C8.2, C9.1, U$1.53 (VDDCORE)
~RESET: C17.2, JP1.11, R8.1, RST0.2 (S), U$1.52 (~RESET)

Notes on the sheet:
ATSAMD51J19
Limor Fried & Dean M.
ESP UART on sercom0 SPI sercom2 DOPO: 0x00 UART sercom3 TXPO: 0x00 I2C sercom5 SPI Flash on QSPI, no longer possible to use with sercom SPI I2S: SCK0: D3 MCK0: D2 FS0: D9 SDI: D1 SDO: D8 SPI1: Sercom1 DOPO: 0x00 SCK: D13 MISO: D12 MOSI: D11 CS: D10 I2C1: A4, A5 PCC: DEN1: MOSI DEN2: SCK CLK: MISO D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
POWER SUPPLY: 3.3V
SERCOM3
ESP3212 MODULE + AUTORESET
SWD Interface
USB Connection & Power
SERCOM5
NEOPIXEL LED
QSPI FLASH
POWER LEDS
